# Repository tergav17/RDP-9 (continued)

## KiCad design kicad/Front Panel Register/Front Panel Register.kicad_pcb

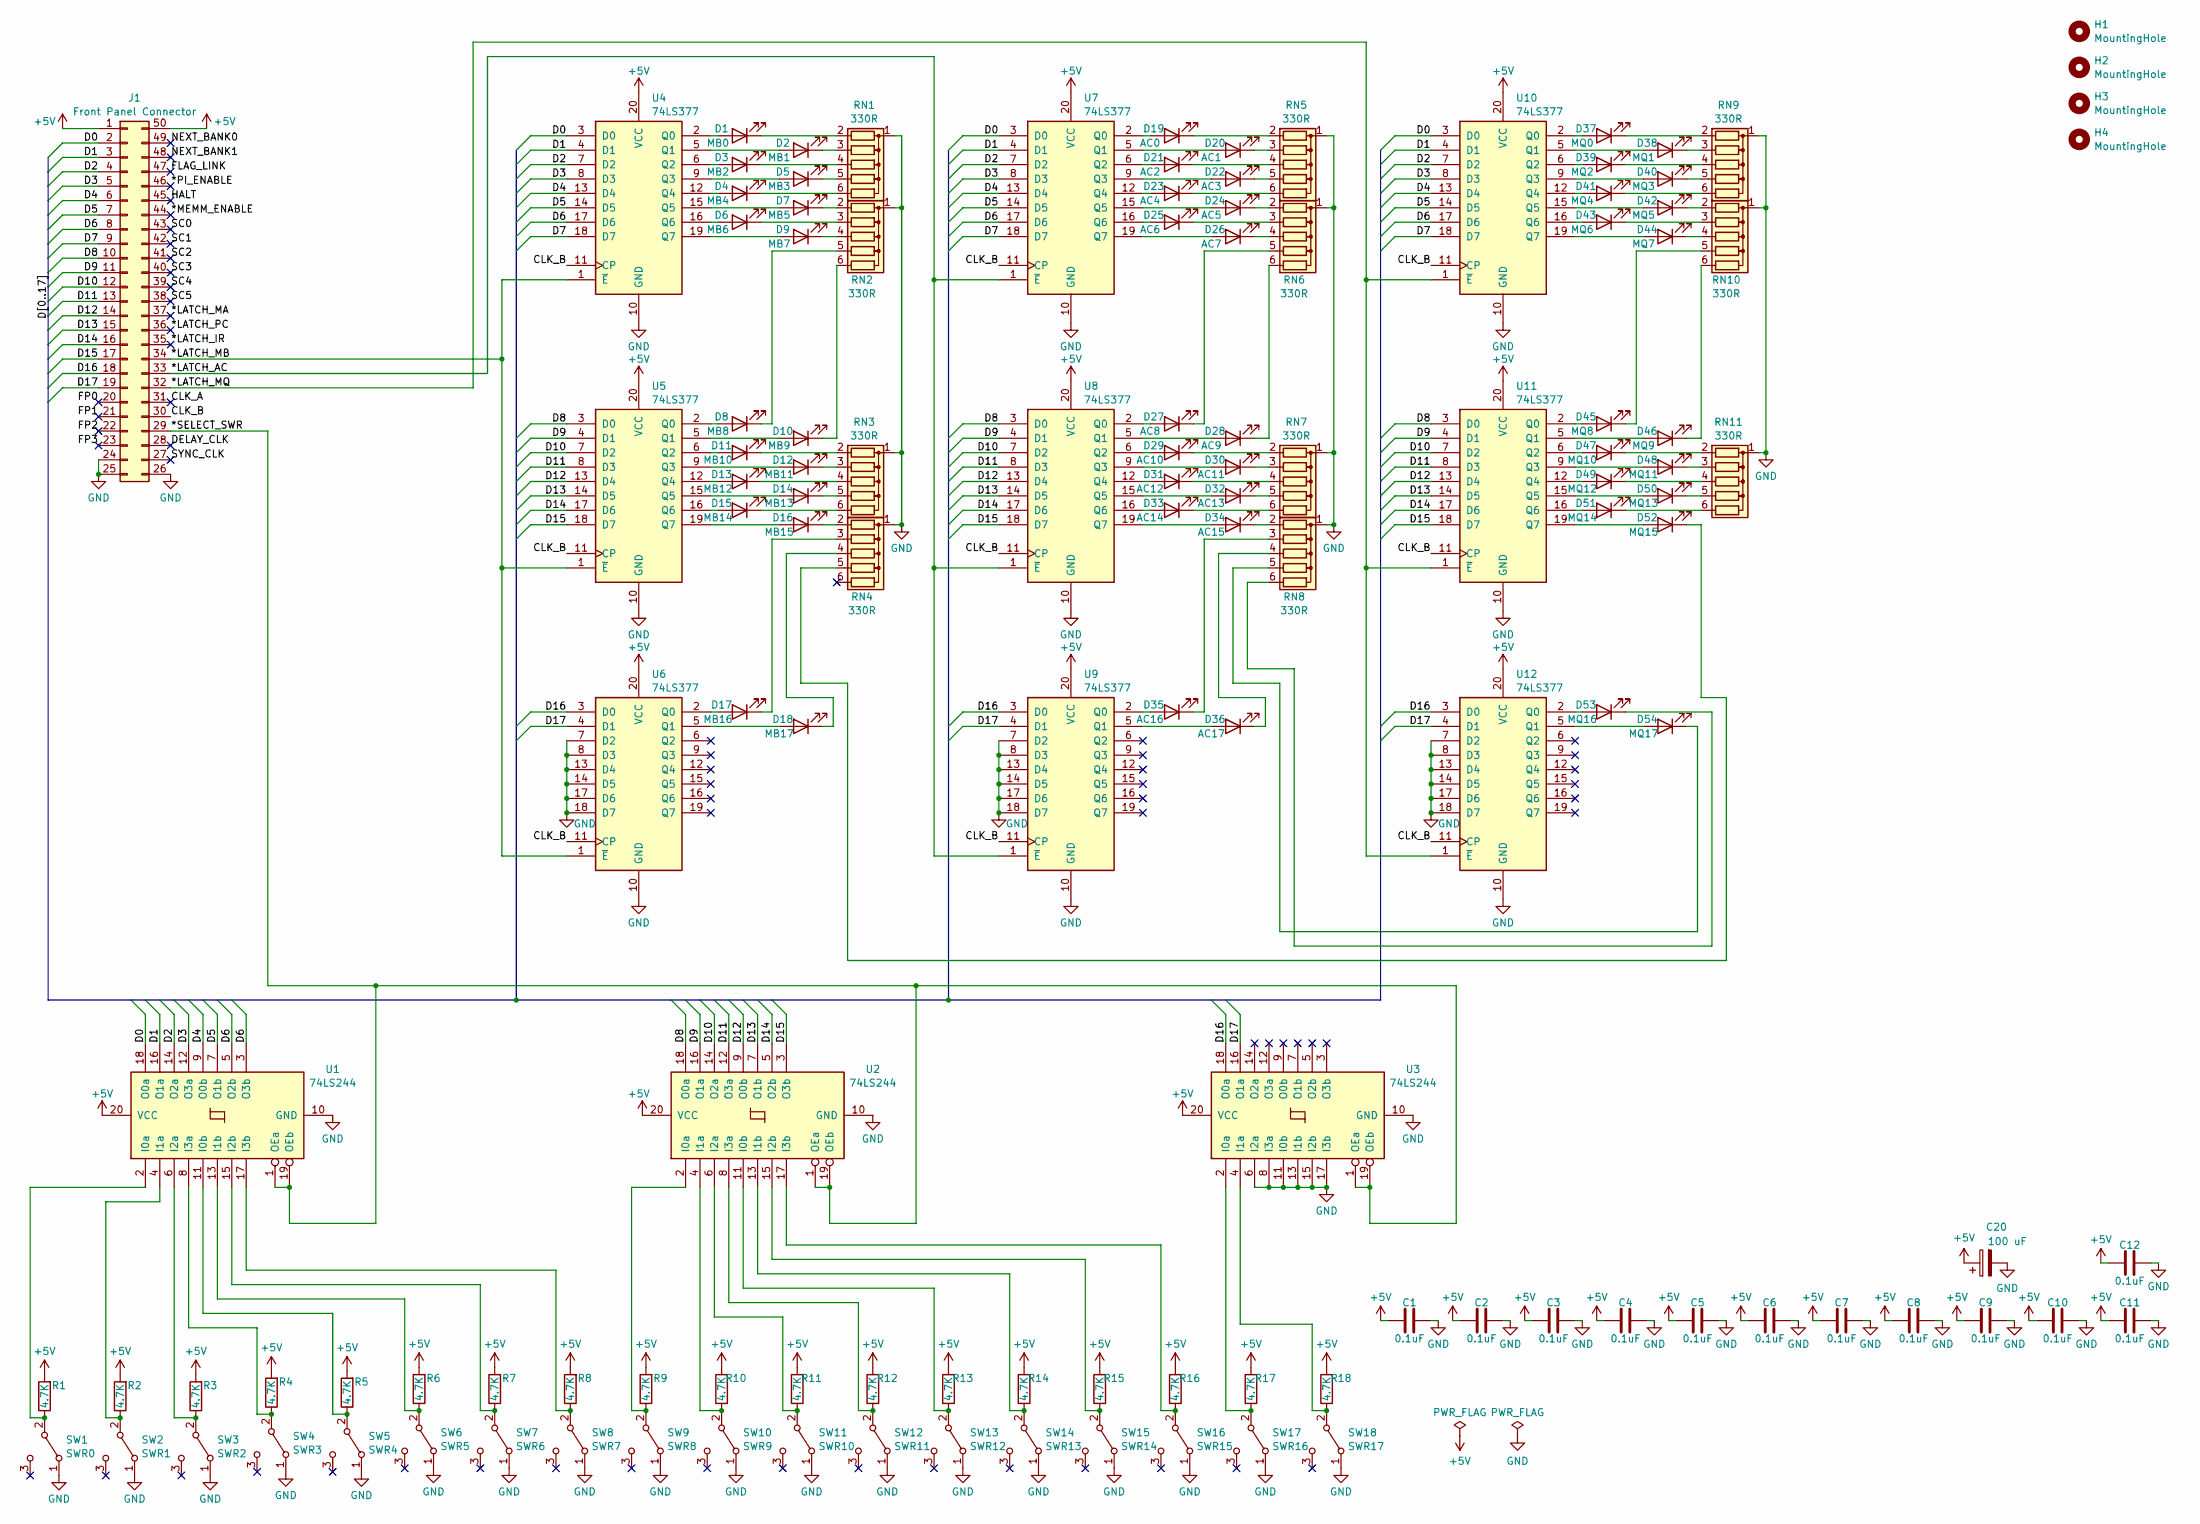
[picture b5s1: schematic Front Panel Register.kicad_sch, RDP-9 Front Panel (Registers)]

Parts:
C1, C2, C3, C4, C5, C6, C7, C8, C9, C10, C11, C12: 0.1uF; C_Disc_D5.0mm_W2.5mm_P5.00mm
C20: 100 uF; CP_Radial_D6.3mm_P2.50mm
D1: MB0; LED_D5.0mm
D2: MB1; LED_D5.0mm
D3: MB2; LED_D5.0mm
D4: MB4; LED_D5.0mm
D5: MB3; LED_D5.0mm
D6: MB6; LED_D5.0mm
D7: MB5; LED_D5.0mm
D8: MB8; LED_D5.0mm
D9: MB7; LED_D5.0mm
D10: MB9; LED_D5.0mm
D11: MB10; LED_D5.0mm
D12: MB11; LED_D5.0mm
D13: MB12; LED_D5.0mm
D14: MB13; LED_D5.0mm
D15: MB14; LED_D5.0mm
D16: MB15; LED_D5.0mm
D17: MB16; LED_D5.0mm
D18: MB17; LED_D5.0mm
D19: AC0; LED_D5.0mm
D20: AC1; LED_D5.0mm
D21: AC2; LED_D5.0mm
D22: AC3; LED_D5.0mm
D23: AC4; LED_D5.0mm
D24: AC5; LED_D5.0mm
D25: AC6; LED_D5.0mm
D26: AC7; LED_D5.0mm
D27: AC8; LED_D5.0mm
D28: AC9; LED_D5.0mm
D29: AC10; LED_D5.0mm
D30: AC11; LED_D5.0mm
D31: AC12; LED_D5.0mm
D32: AC13; LED_D5.0mm
D33: AC14; LED_D5.0mm
D34: AC15; LED_D5.0mm
D35: AC16; LED_D5.0mm
D36: AC17; LED_D5.0mm
D37: MQ0; LED_D5.0mm
D38: MQ1; LED_D5.0mm
D39: MQ2; LED_D5.0mm
D40: MQ3; LED_D5.0mm
D41: MQ4; LED_D5.0mm
D42: MQ5; LED_D5.0mm
D43: MQ6; LED_D5.0mm
D44: MQ7; LED_D5.0mm
D45: MQ8; LED_D5.0mm
D46: MQ9; LED_D5.0mm
D47: MQ10; LED_D5.0mm
D48: MQ11; LED_D5.0mm
D49: MQ12; LED_D5.0mm
D50: MQ13; LED_D5.0mm
D51: MQ14; LED_D5.0mm
D52: MQ15; LED_D5.0mm
D53: MQ16; LED_D5.0mm
D54: MQ17; LED_D5.0mm
H1, H2, H3, H4: MountingHole; MountingHole_2.2mm_M2_Pad
J1: Front Panel Connector; IDC-Header_2x25_P2.54mm_Vertical
R1, R2, R3, R4, R5, R6, R7, R8, R9, R10, R11, R12, R13, R14, R15, R16, R17, R18: 4.7K; R_Axial_DIN0207_L6.3mm_D2.5mm_P7.62mm_Horizontal
RN1, RN2, RN3, RN4, RN5, RN6, RN7, RN8, RN9, RN10, RN11: 330R; R_Array_SIP6
SW1: SWR0; MTS-102
SW2: SWR1; MTS-102
SW3: SWR2; MTS-102
SW4: SWR3; MTS-102
SW5: SWR4; MTS-102
SW6: SWR5; MTS-102
SW7: SWR6; MTS-102
SW8: SWR7; MTS-102
SW9: SWR8; MTS-102
SW10: SWR9; MTS-102
SW11: SWR10; MTS-102
SW12: SWR11; MTS-102
SW13: SWR12; MTS-102
SW14: SWR13; MTS-102
SW15: SWR14; MTS-102
SW16: SWR15; MTS-102
SW17: SWR16; MTS-102
SW18: SWR17; MTS-102
U1, U2, U3: 74LS244; DIP-20_W7.62mm
U4, U5, U6, U7, U8, U9, U10, U11, U12: 74LS377; DIP-20_W7.62mm

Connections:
+5V: C1.1, C2.1, C3.1, C4.1, C5.1, C6.1, C7.1, C8.1, C9.1, C10.1, C11.1, C12.1, J1.1, J1.50, R1.2, R2.2, R3.2, R4.2, R5.2, R6.2, R7.2, R8.2, R9.2, R10.2, R11.2, R12.2, R13.2, R14.2, R15.2, R16.2, R17.2, R18.2, U1.20 (VCC), U2.20 (VCC), U3.20 (VCC), U4.20 (VCC), U5.20 (VCC), U6.20 (VCC), U7.20 (VCC), U8.20 (VCC), U9.20 (VCC), U10.20 (VCC), U11.20 (VCC), U12.20 (VCC); also elsewhere on the board
/*LATCH_AC: J1.33, U7.1 (~E), U8.1 (~E), U9.1 (~E)
/*LATCH_IR: J1.35
/*LATCH_MA: J1.37
/*LATCH_MB: J1.34, U4.1 (~E), U5.1 (~E), U6.1 (~E)
/*LATCH_MQ: J1.32, U10.1 (~E), U11.1 (~E), U12.1 (~E)
/*LATCH_PC: J1.36
/*MEMM_ENABLE: J1.44
/*PI_ENABLE: J1.46
/*SELECT_SWR: J1.29, U1.1 (OEa), U1.19 (OEb), U2.1 (OEa), U2.19 (OEb), U3.1 (OEa), U3.19 (OEb)
/CLK_A: J1.31
/CLK_B: J1.30, U4.11 (CP), U5.11 (CP), U6.11 (CP), U7.11 (CP), U8.11 (CP), U9.11 (CP), U10.11 (CP), U11.11 (CP), U12.11 (CP)
/D0: J1.2, U1.18 (O0a), U4.3 (D0), U7.3 (D0), U10.3 (D0)
/D1: J1.3, U1.16 (O1a), U4.4 (D1), U7.4 (D1), U10.4 (D1)
/D2: J1.4, U1.14 (O2a), U4.7 (D2), U7.7 (D2), U10.7 (D2)
/D3: J1.5, U1.12 (O3a), U4.8 (D3), U7.8 (D3), U10.8 (D3)
/D4: J1.6, U1.9 (O0b), U4.13 (D4), U7.13 (D4), U10.13 (D4)
/D5: J1.7, U1.7 (O1b), U4.14 (D5), U7.14 (D5), U10.14 (D5)
/D6: J1.8, U1.3 (O3b), U1.5 (O2b), U4.17 (D6), U7.17 (D6), U10.17 (D6)
/D7: J1.9, U4.18 (D7), U7.18 (D7), U10.18 (D7)
/D8: J1.10, U2.18 (O0a), U5.3 (D0), U8.3 (D0), U11.3 (D0)
/D9: J1.11, U2.16 (O1a), U5.4 (D1), U8.4 (D1), U11.4 (D1)
/D10: J1.12, U2.14 (O2a), U5.7 (D2), U8.7 (D2), U11.7 (D2)
/D11: J1.13, U2.12 (O3a), U5.8 (D3), U8.8 (D3), U11.8 (D3)
/D12: J1.14, U2.9 (O0b), U5.13 (D4), U8.13 (D4), U11.13 (D4)
/D13: J1.15, U2.7 (O1b), U5.14 (D5), U8.14 (D5), U11.14 (D5)
/D14: J1.16, U2.5 (O2b), U5.17 (D6), U8.17 (D6), U11.17 (D6)
/D15: J1.17, U2.3 (O3b), U5.18 (D7), U8.18 (D7), U11.18 (D7)
/D16: J1.18, U3.18 (O0a), U6.3 (D0), U9.3 (D0), U12.3 (D0)
/D17: J1.19, U3.16 (O1a), U6.4 (D1), U9.4 (D1), U12.4 (D1)
/DELAY_CLK: J1.28
/FLAG_LINK: J1.47
/FP0: J1.20
/FP1: J1.21
/FP2: J1.22
/FP3: J1.23
/HALT: J1.45
/NEXT_BANK0: J1.49
/NEXT_BANK1: J1.48
/SC0: J1.43
/SC1: J1.42
/SC2: J1.41
/SC3: J1.40
/SC4: J1.39
/SC5: J1.38
/SYNC_CLK: J1.27
GND: C1.2, C2.2, C3.2, C4.2, C5.2, C6.2, C7.2, C8.2, C9.2, C10.2, C11.2, C12.2, J1.24, J1.25, J1.26, RN1.1 (common), RN2.1 (common), RN3.1 (common), RN4.1 (common), RN5.1 (common), RN6.1 (common), RN7.1 (common), RN8.1 (common), RN9.1 (common), RN10.1 (common), RN11.1 (common), SW1.1 (A), SW2.1 (A), SW3.1 (A), SW4.1 (A), SW5.1 (A), SW6.1 (A), SW7.1 (A), SW8.1 (A), SW9.1 (A), SW10.1 (A), SW11.1 (A), SW12.1 (A), SW13.1 (A), SW14.1 (A), SW15.1 (A), SW16.1 (A), SW17.1 (A), SW18.1 (A), U1.10 (GND), U2.10 (GND), U3.6 (I2a), U3.8 (I3a), U3.10 (GND), U3.11 (I0b), U3.13 (I1b), U3.15 (I2b), U3.17 (I3b), U4.10 (GND), U5.10 (GND), U6.7 (D2), U6.8 (D3), U6.10 (GND), U6.13 (D4), U6.14 (D5), U6.17 (D6), U6.18 (D7), U7.10 (GND), U8.10 (GND), U9.7 (D2), U9.8 (D3), U9.10 (GND), U9.13 (D4), U9.14 (D5), U9.17 (D6), U9.18 (D7), U10.10 (GND), U11.10 (GND), U12.7 (D2), U12.8 (D3), U12.10 (GND), U12.13 (D4), U12.14 (D5), U12.17 (D6), U12.18 (D7); also elsewhere on the board
unnamed: D1.2 (A), U4.2 (Q0)
unnamed: D1.1 (K), RN1.2 (R1)
unnamed: D2.2 (A), U4.5 (Q1)
unnamed: D2.1 (K), RN1.3 (R2)
unnamed: D3.2 (A), U4.6 (Q2)
unnamed: D3.1 (K), RN1.4 (R3)
unnamed: D4.2 (A), U4.12 (Q4)
unnamed: D4.1 (K), RN1.6 (R5)
unnamed: D5.2 (A), U4.9 (Q3)
unnamed: D5.1 (K), RN1.5 (R4)
unnamed: D6.2 (A), U4.16 (Q6)
unnamed: D6.1 (K), RN2.3 (R2)
unnamed: D7.2 (A), U4.15 (Q5)
unnamed: D7.1 (K), RN2.2 (R1)
unnamed: D8.2 (A), U5.2 (Q0)
unnamed: D8.1 (K), RN2.5 (R4)
unnamed: D9.2 (A), U4.19 (Q7)
unnamed: D9.1 (K), RN2.4 (R3)
unnamed: D10.2 (A), U5.5 (Q1)
unnamed: D10.1 (K), RN2.6 (R5)
unnamed: D11.2 (A), U5.6 (Q2)
unnamed: D11.1 (K), RN3.2 (R1)
unnamed: D12.2 (A), U5.9 (Q3)
unnamed: D12.1 (K), RN3.3 (R2)
unnamed: D13.2 (A), U5.12 (Q4)
unnamed: D13.1 (K), RN3.4 (R3)
unnamed: D14.2 (A), U5.15 (Q5)
unnamed: D14.1 (K), RN3.5 (R4)
unnamed: D15.2 (A), U5.16 (Q6)
unnamed: D15.1 (K), RN3.6 (R5)
unnamed: D16.2 (A), U5.19 (Q7)
unnamed: D16.1 (K), RN4.2 (R1)
unnamed: D17.2 (A), U6.2 (Q0)
unnamed: D17.1 (K), RN4.3 (R2)
unnamed: D18.2 (A), U6.5 (Q1)
unnamed: D18.1 (K), RN4.4 (R3)
unnamed: D19.2 (A), U7.2 (Q0)
unnamed: D19.1 (K), RN5.2 (R1)
unnamed: D20.2 (A), U7.5 (Q1)
unnamed: D20.1 (K), RN5.3 (R2)
unnamed: D21.2 (A), U7.6 (Q2)
unnamed: D21.1 (K), RN5.4 (R3)
unnamed: D22.2 (A), U7.9 (Q3)
unnamed: D22.1 (K), RN5.5 (R4)
unnamed: D23.2 (A), U7.12 (Q4)
unnamed: D23.1 (K), RN5.6 (R5)
unnamed: D24.2 (A), U7.15 (Q5)
unnamed: D24.1 (K), RN6.2 (R1)
unnamed: D25.2 (A), U7.16 (Q6)
unnamed: D25.1 (K), RN6.3 (R2)
unnamed: D26.2 (A), U7.19 (Q7)
unnamed: D26.1 (K), RN6.4 (R3)
unnamed: D27.2 (A), U8.2 (Q0)
unnamed: D27.1 (K), RN6.5 (R4)
unnamed: D28.2 (A), U8.5 (Q1)
unnamed: D28.1 (K), RN6.6 (R5)
unnamed: D29.2 (A), U8.6 (Q2)
unnamed: D29.1 (K), RN7.2 (R1)
unnamed: D30.2 (A), U8.9 (Q3)
unnamed: D30.1 (K), RN7.3 (R2)
unnamed: D31.2 (A), U8.12 (Q4)
unnamed: D31.1 (K), RN7.4 (R3)
unnamed: D32.2 (A), U8.15 (Q5)
unnamed: D32.1 (K), RN7.5 (R4)
unnamed: D33.2 (A), U8.16 (Q6)
unnamed: D33.1 (K), RN7.6 (R5)
unnamed: D34.2 (A), U8.19 (Q7)
unnamed: D34.1 (K), RN8.2 (R1)
unnamed: D35.2 (A), U9.2 (Q0)
unnamed: D35.1 (K), RN8.3 (R2)
unnamed: D36.2 (A), U9.5 (Q1)
unnamed: D36.1 (K), RN8.4 (R3)
unnamed: D37.2 (A), U10.2 (Q0)
unnamed: D37.1 (K), RN9.2 (R1)
unnamed: D38.2 (A), U10.5 (Q1)
unnamed: D38.1 (K), RN9.3 (R2)
unnamed: D39.2 (A), U10.6 (Q2)
unnamed: D39.1 (K), RN9.4 (R3)
unnamed: D40.2 (A), U10.9 (Q3)
unnamed: D40.1 (K), RN9.5 (R4)
unnamed: D41.2 (A), U10.12 (Q4)
unnamed: D41.1 (K), RN9.6 (R5)
unnamed: D42.2 (A), U10.15 (Q5)
unnamed: D42.1 (K), RN10.2 (R1)
unnamed: D43.2 (A), U10.16 (Q6)
unnamed: D43.1 (K), RN10.3 (R2)
unnamed: D44.2 (A), U10.19 (Q7)
unnamed: D44.1 (K), RN10.4 (R3)
unnamed: D45.2 (A), U11.2 (Q0)
unnamed: D45.1 (K), RN10.5 (R4)
unnamed: D46.2 (A), U11.5 (Q1)
unnamed: D46.1 (K), RN10.6 (R5)
unnamed: D47.2 (A), U11.6 (Q2)
unnamed: D47.1 (K), RN11.2 (R1)
unnamed: D48.2 (A), U11.9 (Q3)
unnamed: D48.1 (K), RN11.3 (R2)
unnamed: D49.2 (A), U11.12 (Q4)
unnamed: D49.1 (K), RN11.4 (R3)
unnamed: D50.2 (A), U11.15 (Q5)
unnamed: D50.1 (K), RN11.5 (R4)
unnamed: D51.2 (A), U11.16 (Q6)
unnamed: D51.1 (K), RN11.6 (R5)
unnamed: D52.2 (A), U11.19 (Q7)
unnamed: D52.1 (K), RN4.5 (R4)
unnamed: D53.2 (A), U12.2 (Q0)
unnamed: D53.1 (K), RN8.6 (R5)
unnamed: D54.2 (A), U12.5 (Q1)
unnamed: D54.1 (K), RN8.5 (R4)
unnamed: R1.1, SW1.2 (B), U1.2 (I0a)
unnamed: R2.1, SW2.2 (B), U1.4 (I1a)
unnamed: R3.1, SW3.2 (B), U1.6 (I2a)
unnamed: R4.1, SW4.2 (B), U1.8 (I3a)
unnamed: R5.1, SW5.2 (B), U1.11 (I0b)
unnamed: R6.1, SW6.2 (B), U1.13 (I1b)
unnamed: R7.1, SW7.2 (B), U1.15 (I2b)
unnamed: R8.1, SW8.2 (B), U1.17 (I3b)
unnamed: R9.1, SW9.2 (B), U2.2 (I0a)
unnamed: R10.1, SW10.2 (B), U2.4 (I1a)
unnamed: R11.1, SW11.2 (B), U2.6 (I2a)
unnamed: R12.1, SW12.2 (B), U2.8 (I3a)
unnamed: R13.1, SW13.2 (B), U2.11 (I0b)
unnamed: R14.1, SW14.2 (B), U2.13 (I1b)
unnamed: R15.1, SW15.2 (B), U2.15 (I2b)
unnamed: R16.1, SW16.2 (B), U2.17 (I3b)
unnamed: R17.1, SW17.2 (B), U3.2 (I0a)
unnamed: R18.1, SW18.2 (B), U3.4 (I1a)

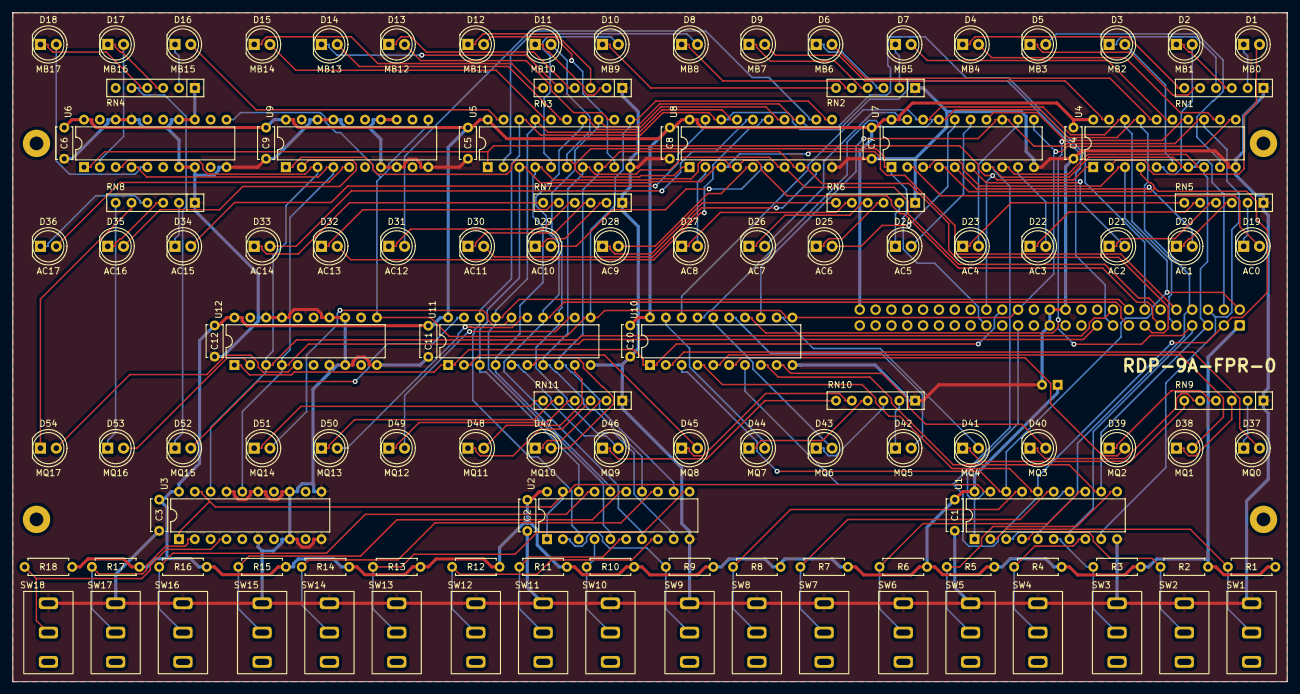
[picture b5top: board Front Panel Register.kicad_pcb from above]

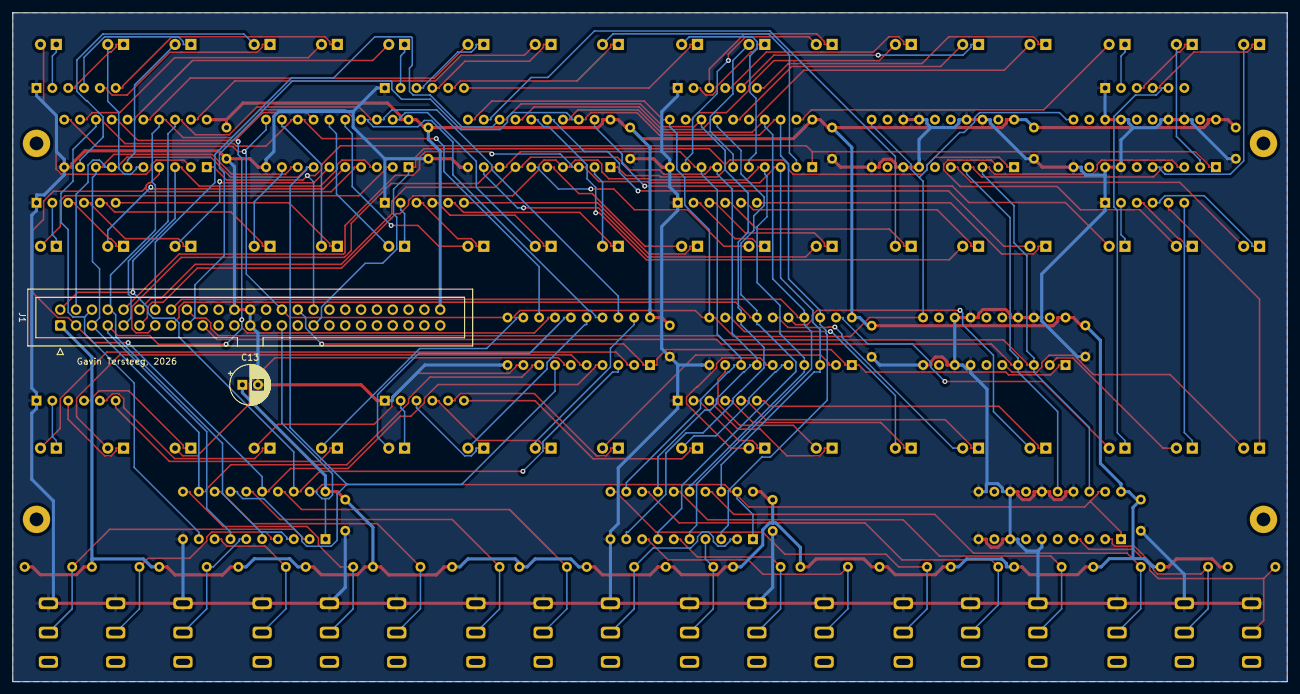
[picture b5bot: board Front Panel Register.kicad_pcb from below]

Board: 2 copper layers, 204.5 x 107.3 mm, 131 parts (2 on the bottom side), 151 nets.

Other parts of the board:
C13: 100 uF; CP_Radial_D6.3mm_P2.50mm

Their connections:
+5V: C13.1; also elsewhere on the board
GND: C13.2; also elsewhere on the board
